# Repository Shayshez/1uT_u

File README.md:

# 1uT_u
1u Version (Pulp Logic) of Temps Utile, 30HP.

For pcb's and panels: https://pushermanproductions.com/product/plum-audio-1u-temps-utile-pcb-and-aluminium-panel-30hp/

Teensy Assembling (with Supervisor):https://youtu.be/IDsQhNgkL-Y

OLED Screen Assembling: https://youtu.be/ywh_6SPNrSg 

** Note for Pusherman v1.0 Pcb's - There is minor silk screen mistake - The Inputs and Outputs not numberd correctly.

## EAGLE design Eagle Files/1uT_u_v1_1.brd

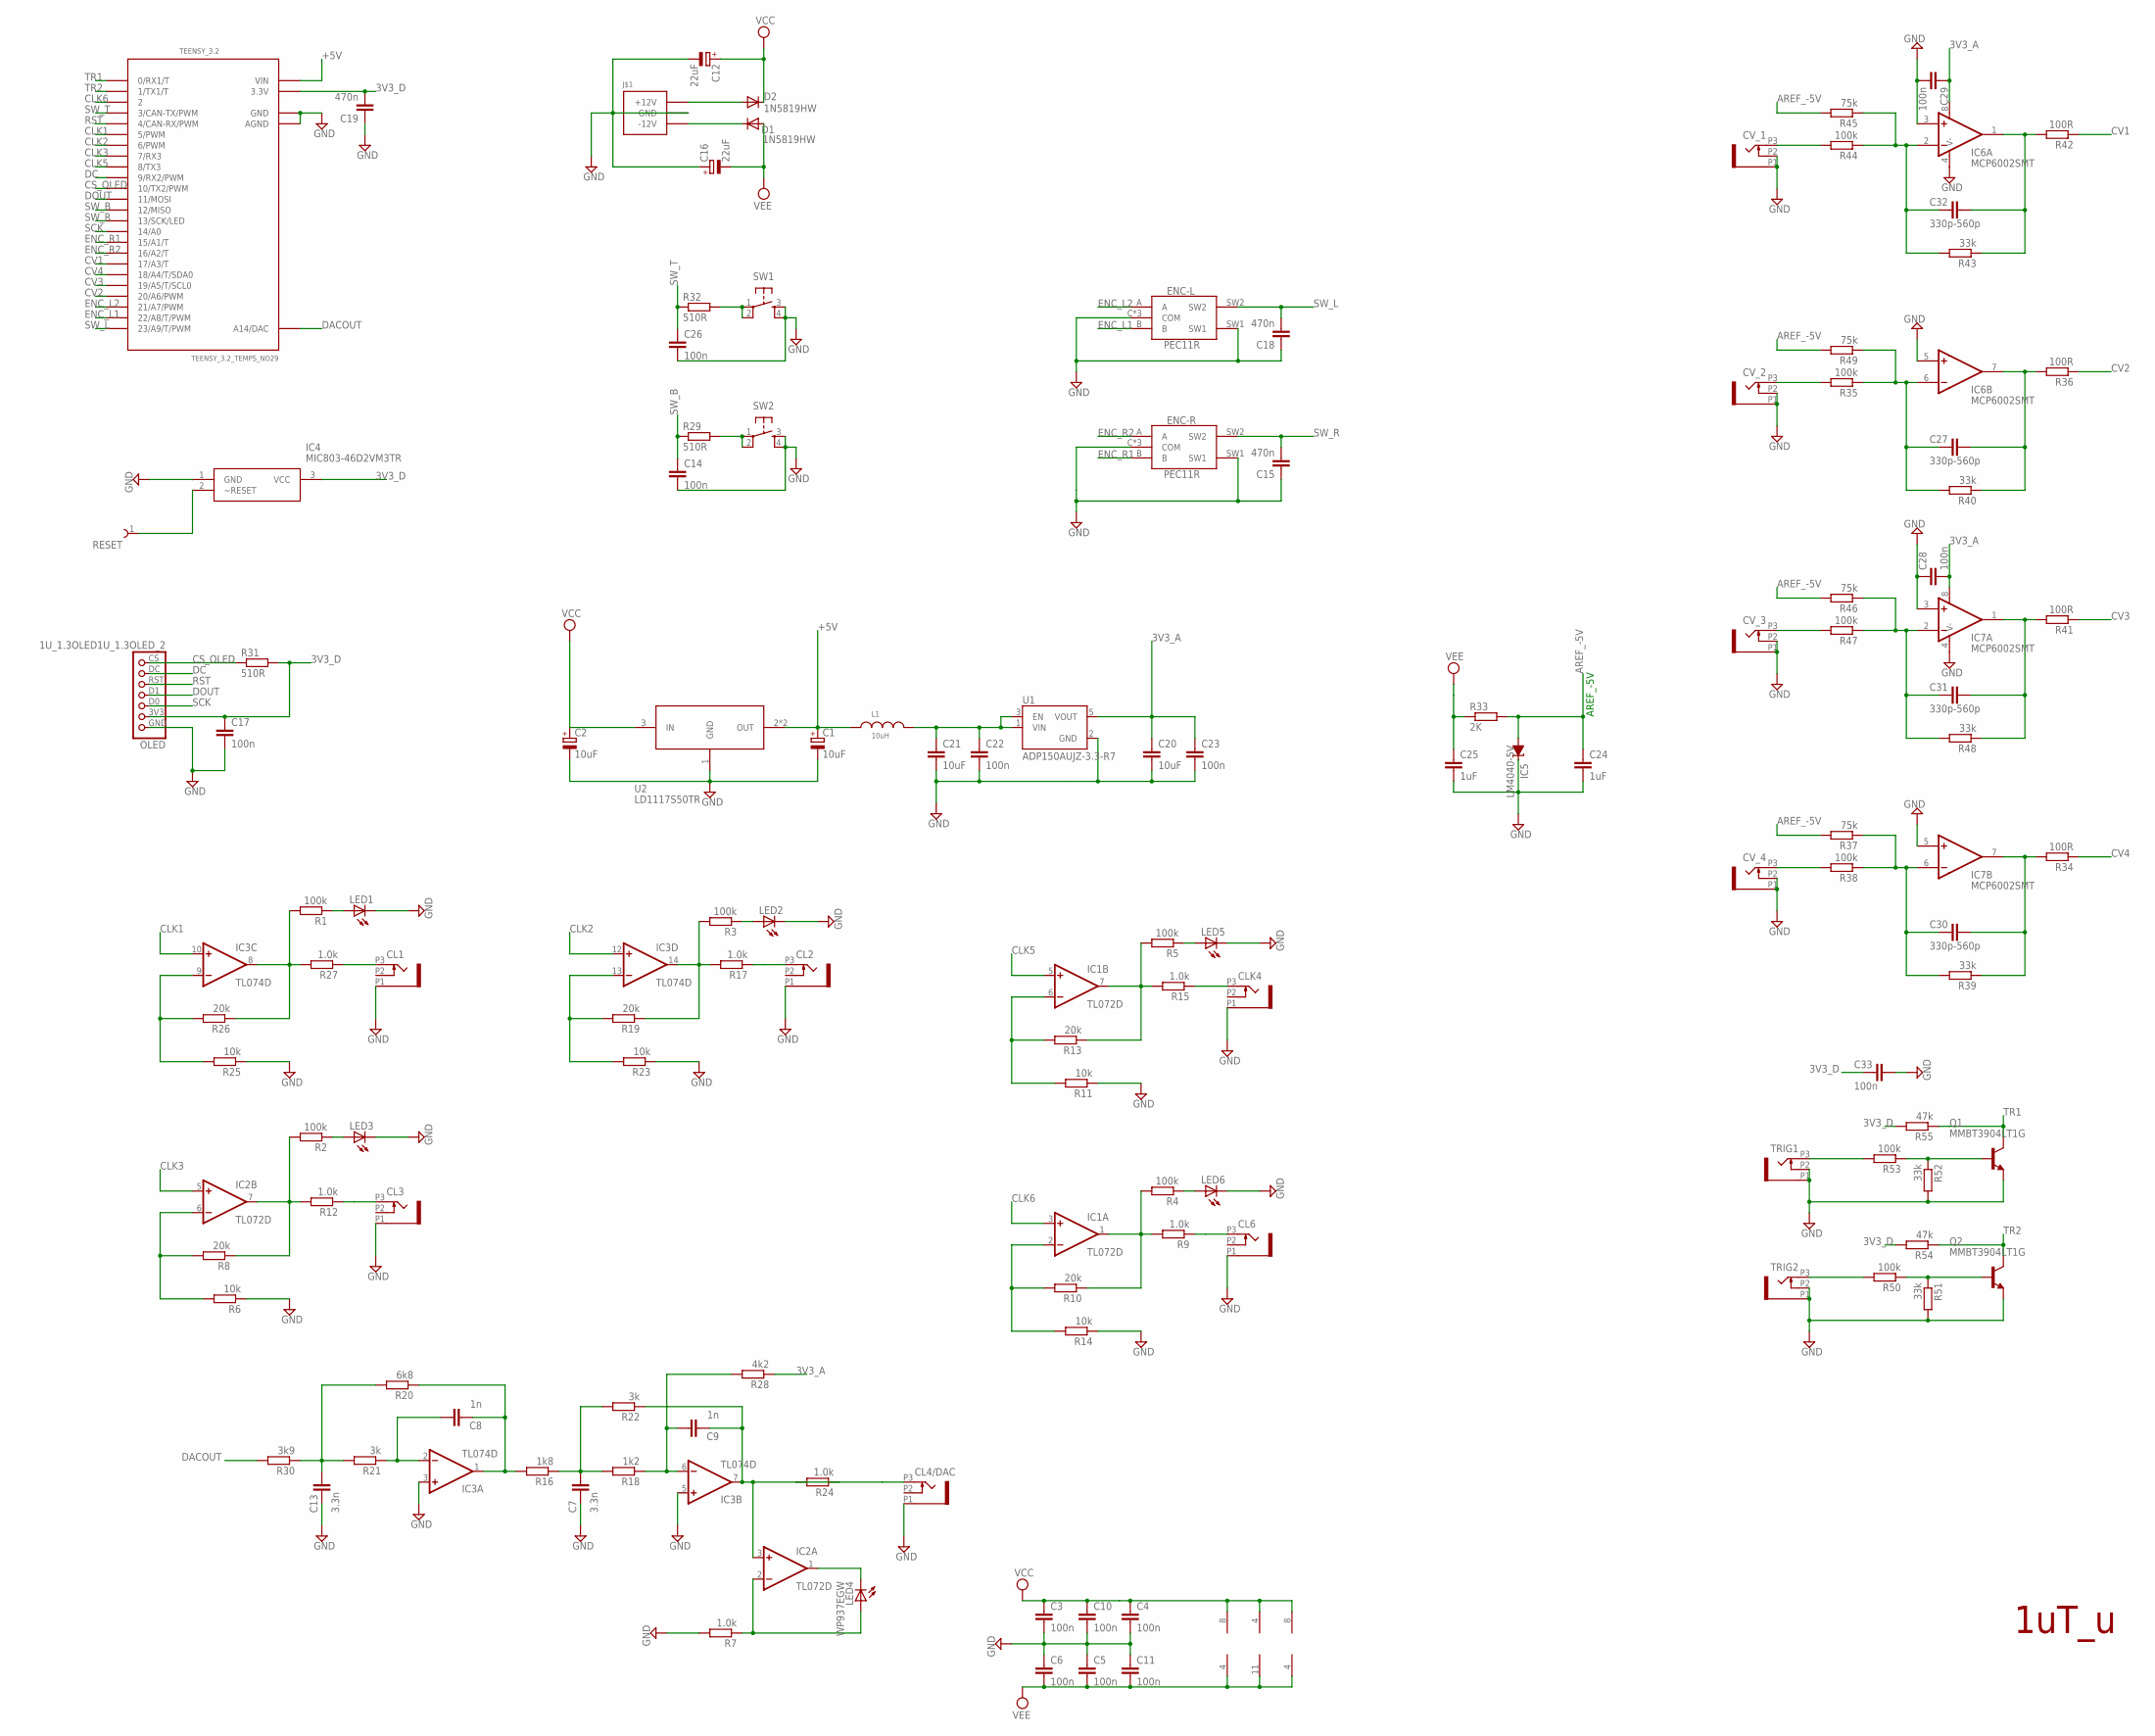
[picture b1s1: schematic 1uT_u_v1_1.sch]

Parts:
C1, C2: 10uF; PANASONIC_B
C3, C4, C5, C6, C10, C11, C14, C17, C22, C23, C26, C28, C29, C33: 100n; C0603
C7, C13: 3.3n; C0603
C8, C9: 1n; C0603
C12, C16: 22uF; PANASONIC_C
C15, C18, C19: 470n; C0603
C20, C21: 10uF; C1206K
C24, C25: 1uF; C0603
C27, C30, C31, C32: 330p-560p; C0603
CL1, CL2, CL3, CL4/DAC, CL6: OG-PJ301_PJ301_THONKICONN; OG-PJ301_WQP_PJ_301M6_NO_HOLE
CLK4: OG-PJ301_PJ301_THONKICONN; OG-PJ301_WQP_PJ_301M6_NO_HOLE
CV_1, CV_2, CV_3, CV_4: OG-PJ301_PJ301_THONKICONN; OG-PJ301_WQP_PJ_301M6_NO_HOLE
D1, D2: 1N5819HW; DIODE_SOD123
ENC-L: PEC11R; PEC11R-4XXXK-SXXXX
ENC-R: PEC11R; PEC11R-4XXXK-SXXXX
IC1, IC2: TL072D; SO08
IC3: TL074D; SO14
IC4: MIC803-46D2VM3TR; SOT95P230X110-3N
IC5: LM4040-5V; DBZ_R-PDSO-G3
IC6, IC7: MCP6002SMT; SOIC8
J$1: POWER_SIMPLE10; POWER_10
L1: 10uH; WE-LQ_M
LED1, LED2, LED3, LED5, LED6: LED3MM
LED4: WP937EGW; LED3MM
OLED: 1U_1.3OLED1U_1.3OLED_2; 1U_1.3OLED_2
Q1, Q2: MMBT3904LT1G; TRANSISTOR_SOT23-BEC
R1, R2, R3, R4, R5, R35, R38, R44, R47, R50, R53: 100k; R0603
R6, R11, R14, R23, R25: 10k; R0603
R7, R9, R12, R15, R17, R24, R27: 1.0k; R0603
R8, R10, R13, R19, R26: 20k; R0603
R16: 1k8; R0603
R18: 1k2; R0603
R20: 6k8; R0603
R21, R22: 3k; R0603
R28: 4k2; R0603
R29, R31, R32: 510R; R0603
R30: 3k9; R0603
R33: 2K; R0603
R34, R36, R41, R42: 100R; R0603
R37, R45, R46, R49: 75k; R0603
R39, R40, R43, R48, R51, R52: 33k; R0603
R54, R55: 47k; R0603
RESET: 61300111121
SW1, SW2: TAC_SWITCHPTH; TACTILE-PTH
TEENSY_3.2: TEENSY_3.2_TEMPS_NO29
TRIG1, TRIG2: OG-PJ301_PJ301_THONKICONN; OG-PJ301_WQP_PJ_301M6_NO_HOLE
U1: ADP150AUJZ-3.3-R7; SOT95P280X100-5N
U2: LD1117S50TR; SOT223

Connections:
3V3_A: C20.1, C23.1, C28.2, C29.1, IC6.8 (V+), IC7.8 (V+), R28.1, U1.5 (VOUT)
3V3_D: C17.1, C19.2, C33.2, IC4.3 (VCC), OLED.3V3, R31.2, R54.2, R55.2, TEENSY_3.2.3.3V
+5V: C1.+, L1.1, TEENSY_3.2.VIN, U2.2 (OUT), U2.4 (OUT)
AREF_-5V: C24.1, IC5.2 (A), R33.2, R37.2, R45.2, R46.2, R49.2
CLK1: IC3.10 (+IN), TEENSY_3.2.5 (5/PWM)
CLK2: IC3.12 (+IN), TEENSY_3.2.6 (6/PWM)
CLK3: IC2.5 (+IN), TEENSY_3.2.7 (7/RX3)
CLK5: IC1.5 (+IN), TEENSY_3.2.8 (8/TX3)
CLK6: IC1.3 (+IN), TEENSY_3.2.2
CS_OLED: OLED.CS, R31.1, TEENSY_3.2.10 (10/TX2/PWM)
CV1: R42.1, TEENSY_3.2.17/A3 (17/A3/T)
CV2: R36.1, TEENSY_3.2.20/A6 (20/A6/PWM)
CV3: R41.1, TEENSY_3.2.19/A5 (19/A5/T/SCL0)
CV4: R34.1, TEENSY_3.2.18/A4 (18/A4/T/SDA0)
DACOUT: R30.2, TEENSY_3.2.RESET/DAC (A14/DAC)
DC: OLED.DC, TEENSY_3.2.9 (9/RX2/PWM)
DOUT: OLED.D1, TEENSY_3.2.11 (11/MOSI)
ENC_L1: ENC-L.B, TEENSY_3.2.22/A8 (22/A8/T/PWM)
ENC_L2: ENC-L.A, TEENSY_3.2.21/A7 (21/A7/PWM)
ENC_R1: ENC-R.B, TEENSY_3.2.15/A1 (15/A1/T)
ENC_R2: ENC-R.A, TEENSY_3.2.16/A2 (16/A2/T)
GND: C1.-, C2.-, C3.2, C4.2, C5.1, C6.1, C7.2, C10.2, C11.1, C12.-, C13.2, C14.2, C15.1, C16.+, C17.2, C18.1, C19.1, C20.2, C21.2, C22.2, C23.2, C24.2, C25.2, C26.2, C28.1, C29.2, C33.1, CL1.P1 (1), CL2.P1 (1), CL3.P1 (1), CL4/DAC.P1 (1), CL6.P1 (1), CLK4.P1 (1), CV_1.P1 (1), CV_1.P2 (2), CV_2.P1 (1), CV_2.P2 (2), CV_3.P1 (1), CV_3.P2 (2), CV_4.P1 (1), CV_4.P2 (2), ENC-L.C (COM), ENC-L.SH1 (COM), ENC-L.SH2 (COM), ENC-L.SW1, ENC-R.C (COM), ENC-R.SH1 (COM), ENC-R.SH2 (COM), ENC-R.SW1, IC3.3 (+IN), IC3.5 (+IN), IC4.1 (GND), IC5.1 (C), IC6.3 (+IN), IC6.4 (V-), IC6.5 (+IN), IC7.3 (+IN), IC7.4 (V-), IC7.5 (+IN), J$1.3 (GND), J$1.4 (GND), J$1.5 (GND), J$1.6 (GND), J$1.7 (GND), J$1.8 (GND), LED1.K (C), LED2.K (C), LED3.K (C), LED5.K (C), LED6.K (C), OLED.GND, Q1.E, Q2.E, R6.1, R7.2, R11.1, R14.1, R23.1, R25.1, R51.2, R52.2, SW1.3, SW1.4, SW2.3, SW2.4, TEENSY_3.2.AGND, TEENSY_3.2.GND, TRIG1.P1 (1), TRIG1.P2 (2), TRIG2.P1 (1), TRIG2.P2 (2), U1.2 (GND), U2.1 (GND)
unnamed: D2.A, J$1.9 (+12V), J$1.10 (+12V)
unnamed: C21.1, C22.1, L1.2, U1.1 (VIN), U1.3 (EN)
unnamed: CV_1.P3 (3), R44.2
unnamed: C32.2, IC6.2 (-IN), R43.2, R44.1, R45.1
unnamed: C32.1, IC6.1 (OUT), R42.2, R43.1
unnamed: R32.2, SW1.1, SW1.2
unnamed: CV_2.P3 (3), R35.2
unnamed: R29.2, SW2.1, SW2.2
unnamed: C27.2, IC6.6 (-IN), R35.1, R40.2, R49.1
unnamed: C27.1, IC6.7 (OUT), R36.2, R40.1
unnamed: CV_3.P3 (3), R47.2
unnamed: C31.2, IC7.2 (-IN), R46.1, R47.1, R48.2
unnamed: C31.1, IC7.1 (OUT), R41.2, R48.1
unnamed: CV_4.P3 (3), R38.2
unnamed: C30.2, IC7.6 (-IN), R37.1, R38.1, R39.2
unnamed: C30.1, IC7.7 (OUT), R34.2, R39.1
unnamed: R53.2, TRIG1.P3 (3)
unnamed: Q1.B, R52.1, R53.1
unnamed: R50.2, TRIG2.P3 (3)
unnamed: Q2.B, R50.1, R51.1
unnamed: CL1.P3 (3), R27.1
unnamed: CL3.P3 (3), R12.1
unnamed: IC1.6 (-IN), R11.2, R13.2
unnamed: IC1.7 (OUT), R5.2, R13.1, R15.2
unnamed: IC3.13 (-IN), R19.2, R23.2
unnamed: IC3.9 (-IN), R25.2, R26.2
unnamed: IC3.8 (OUT), R1.2, R26.1, R27.2
unnamed: CLK4.P3 (3), R15.1
unnamed: IC3.14 (OUT), R3.2, R17.2, R19.1
unnamed: CL2.P3 (3), R17.1
unnamed: IC2.6 (-IN), R6.2, R8.2
unnamed: IC2.7 (OUT), R2.2, R8.1, R12.2
unnamed: IC1.2 (-IN), R10.2, R14.2
unnamed: IC2.1 (OUT), LED4.K (C)
unnamed: IC2.2 (-IN), LED4.A, R7.1
unnamed: CL4/DAC.P3 (3), R24.1
unnamed: IC1.1 (OUT), R4.2, R9.2, R10.1
unnamed: CL6.P3 (3), R9.1
unnamed: C9.2, IC2.3 (+IN), IC3.7 (OUT), R22.1, R24.2
unnamed: D1.C, J$1.1 (-12V), J$1.2 (-12V)
unnamed: C13.1, R20.2, R21.2, R30.1
unnamed: C8.1, IC3.2 (-IN), R21.1
unnamed: C8.2, IC3.1 (OUT), R16.2, R20.1
unnamed: C7.1, R16.1, R18.2, R22.2
unnamed: C9.1, IC3.6 (-IN), R18.1, R28.2
unnamed: LED3.A, R2.1
unnamed: LED1.A, R1.1
unnamed: LED2.A, R3.1
unnamed: LED5.A, R5.1
unnamed: LED6.A, R4.1
unnamed: IC4.2 (~RESET), RESET.1
RST: OLED.RST, TEENSY_3.2.4 (4/CAN-RX/PWM)
SCK: OLED.D0, TEENSY_3.2.14/A0
SW_B: C14.1, R29.1, TEENSY_3.2.12 (12/MISO)
SW_L: C18.2, ENC-L.SW2, TEENSY_3.2.23/A9 (23/A9/T/PWM)
SW_R: C15.2, ENC-R.SW2, TEENSY_3.2.13 (13/SCK/LED)
SW_T: C26.1, R32.1, TEENSY_3.2.3 (3/CAN-TX/PWM)
TR1: Q1.C, R55.1, TEENSY_3.2.0 (0/RX1/T)
TR2: Q2.C, R54.1, TEENSY_3.2.1 (1/TX1/T)
VCC: C2.+, C3.1, C4.1, C10.1, C12.+, D2.C, IC1.8 (V+), IC2.8 (V+), IC3.4 (V+), U2.3 (IN)
VEE: C5.2, C6.2, C11.2, C16.-, C25.1, D1.A, IC1.4 (V-), IC2.4 (V-), IC3.11 (V-), R33.1

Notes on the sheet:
AREF_-5V
1uT_u

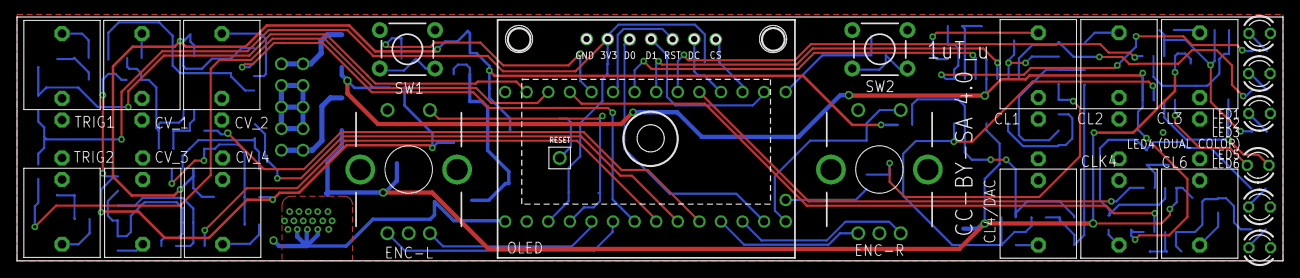
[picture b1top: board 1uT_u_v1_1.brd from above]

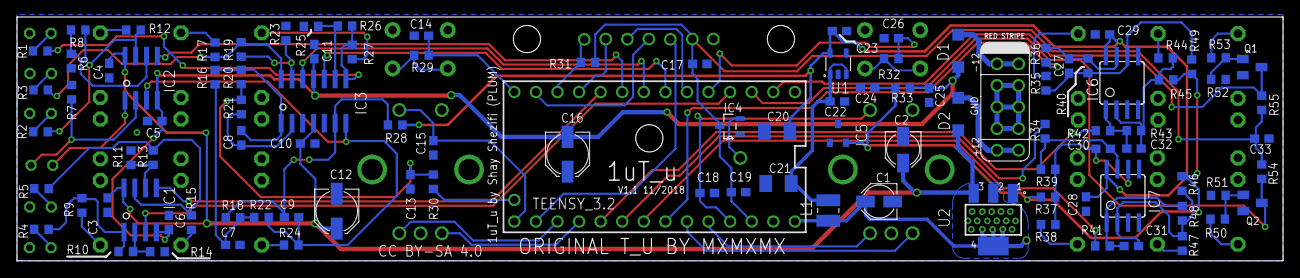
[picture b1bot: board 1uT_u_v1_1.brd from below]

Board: 2 copper layers, 149.0 x 28.7 mm, 128 parts (104 on the bottom side), 83 nets.

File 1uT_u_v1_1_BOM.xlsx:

Qty | Value | Device | Package |  | Parts | Description | ALLIED_NUMBER | ALLIED_PRICE-STOCK | ARROW_PART_NUMBER | ARROW_PRICE-STOCK | AVAILABILITY | DESCRIPTION | HEIGHT | MANUFACTURER_NAME | MANUFACTURER_PART_NUMBER | MF | MP | MPN | OC_FARNELL | OC_NEWARK | PACKAGE | PRICE | RS_PART_NUMBER | RS_PRICE-STOCK | SPICEPREFIX | WE-NUMBER
4 | 100R | R-EU_R0603 | R0603 | 603-RC0603FR-07100RL | R34, R36, R41, R42 | RESISTOR, European symbol |  |  |  |  |  |  |  |  |  |  |  |  |  |  |  |  |  |  | R
3 | 510R | R-EU_R0603 | R0603 | 603-RC0603FR-07510RL | R29, R31, R32 | RESISTOR, European symbol |  |  |  |  |  |  |  |  |  |  |  |  |  |  |  |  |  |  | R
7 | 1.0k | R-EU_R0603 | R0603 | 603-RC0603FR-071KL | R7, R9, R12, R15, R17, R24, R27 | RESISTOR, European symbol |  |  |  |  |  |  |  |  |  |  |  |  |  |  |  |  |  |  | R
1 | 1k2 | R-EU_R0603 | R0603 | 603-RC0603FR-101K2L | R18 | RESISTOR, European symbol |  |  |  |  |  |  |  |  |  |  |  |  |  |  |  |  |  |  | R
1 | 1k8 | R-EU_R0603 | R0603 | 603-RC0603FR-071K8L | R16 | RESISTOR, European symbol |  |  |  |  |  |  |  |  |  |  |  |  |  |  |  |  |  |  | R
1 | 2K | R-EU_R0603 | R0603 | 603-RC0603FR-102KL | R33 | RESISTOR, European symbol |  |  |  |  |  |  |  |  |  |  |  |  |  |  |  |  |  |  | R
2 | 3k | R-EU_R0603 | R0603 | 603-RC0603FR-073KL | R21, R22 | RESISTOR, European symbol |  |  |  |  |  |  |  |  |  |  |  |  |  |  |  |  |  |  | R
1 | 3k9 | R-EU_R0603 | R0603 | 603-RC0603FR-133K9L | R30 | RESISTOR, European symbol |  |  |  |  |  |  |  |  |  |  |  |  |  |  |  |  |  |  | R
1 | 4k2 | R-EU_R0603 | R0603 | 603-RC0603FR-074K22L | R28 | RESISTOR, European symbol |  |  |  |  |  |  |  |  |  |  |  |  |  |  |  |  |  |  | R
1 | 6k8 | R-EU_R0603 | R0603 | 603-RC0603FR-106K8L | R20 | RESISTOR, European symbol |  |  |  |  |  |  |  |  |  |  |  |  |  |  |  |  |  |  | R
5 | 10k | R-EU_R0603 | R0603 | 603-RC0603FR-0710KL | R6, R11, R14, R23, R25 | RESISTOR, European symbol |  |  |  |  |  |  |  |  |  |  |  |  |  |  |  |  |  |  | R
5 | 20k | R-EU_R0603 | R0603 | 603-RC0603FR-1020KL | R8, R10, R13, R19, R26 | RESISTOR, European symbol |  |  |  |  |  |  |  |  |  |  |  |  |  |  |  |  |  |  | R
6 | 33k | R-EU_R0603 | R0603 | 603-RC0603FR-0733KL | R39, R40, R43, R48, R51, R52 | RESISTOR, European symbol |  |  |  |  |  |  |  |  |  |  |  |  |  |  |  |  |  |  | R
2 | 47k | R-EU_R0603 | R0603 | 603-RC0603FR-0747KL | R54, R55 | RESISTOR, European symbol |  |  |  |  |  |  |  |  |  |  |  |  |  |  |  |  |  |  | R
4 | 75k | R-EU_R0603 | R0603 | 603-AC0603FR-0775KL | R37, R45, R46, R49 | RESISTOR, European symbol |  |  |  |  |  |  |  |  |  |  |  |  |  |  |  |  |  |  | R
11 | 100k | R-EU_R0603 | R0603 | 603-RC0603FR-07100KL | R1, R2, R3, R4, R5, R35, R38, R44, R47, R50, R53 | RESISTOR, European symbol |  |  |  |  |  |  |  |  |  |  |  |  |  |  |  |  |  |  | R
4 | 330p-560p | C-EUC0603 | C0603 |  | C27, C30, C31, C32 | CAPACITOR, European symbol
2 | 1n | C-EUC0603 | C0603 |  | C8, C9 | CAPACITOR, European symbol
2 | 3.3n | C-EUC0603 | C0603 |  | C7, C13 | CAPACITOR, European symbol
14 | 100n | C-EUC0603 | C0603 |  | C3, C4, C5, C6, C10, C11, C14, C17, C22, C23, C26, C28, C29, C33 | CAPACITOR, European symbol
3 | 470n | C-EUC0603 | C0603 |  | C15, C18, C19 | CAPACITOR, European symbol
2 | 1uF | C-EUC0603 | C0603 |  | C24, C25 | CAPACITOR, European symbol
2 | 10uF | C-EUC1206K | C1206K |  | C20, C21 | CAPACITOR, European symbol
2 | 10uF | CPOL-EUB | PANASONIC_B |  | C1, C2 | POLARIZED CAPACITOR, European symbol |  |  |  |  |  |  |  |  |  |  |  |  |  |  |  |  |  |  | C
2 | 22uF | CPOL-EUC | PANASONIC_C |  | C12, C16 | POLARIZED CAPACITOR, European symbol |  |  |  |  |  |  |  |  |  |  |  |  |  |  |  |  |  |  | C
2 | 1N5819HW | DIODE_DIODE-SOD123 | DIODE_SOD123 |  | D1, D2 | DIODE
1 | 10uH | WE-LQ_1210_744032001 | WE-LQ_M | 963-LB3218T100K | L1 | SMD Inductor |  |  |  |  |  |  |  |  |  |  |  |  |  |  |  |  |  |  |  | 744032001/1uH
1 | LM4040-5V | LM4041B12DBZ | DBZ_R-PDSO-G3 |  | IC5 | PRECISION MICROPOWER SHUNT VOLTAGE REFERENCE |  |  |  |  |  |  |  |  |  |  |  | LM4041B12IDBZR | 1575212 | 58K5882
2 | TL072D | TL072D | SO08 |  | IC1, IC2 | OP AMP
1 | TL074D | TL074D | SO14 |  | IC3 | OP AMP
2 | MCP6002SMT | MCP6002SMT | SOIC8 |  | IC6, IC7 | Dual General Op Amp
1 | LD1117S50TR | LD1117S50TR | SOT223 |  | U2 | http://octopart.com/ld1117s50tr-stmicroelectronics-529395 |  |  |  |  | Good | LD1117 Series 1300 mA 5 V Fixed Output Positive Voltage LDO Regulator - SOT-223 |  |  |  | STMicroelectronics | LD1117S50TR |  |  |  | SOT-223 STMicroelectronics | 0.19 USD
2 | MMBT3904LT1G | TRANSISTOR_MMBT3904LT1-NPN-SOT23-BEC | TRANSISTOR_SOT23-BEC |  | Q1, Q2 | NPN Transistror
1 | MIC803-46D2VM3TR | MIC803-46D2VM3TR | SOT95P230X110-3N |  | IC4 | 3-pin Microprocessor Supervosor Circui |  |  | MIC803-46D2VM3TR |  |  | 3-pin Microprocessor Supervosor Circui | mm | Micrel | MIC803-46D2VM3TR
1 | ADP150AUJZ-3.3-R7 | ADP150AUJZ-3.3-R7 | SOT95P280X100-5N |  | U1 | IC REG LINEAR 2V 150MA 5TSOT |  |  |  |  | Good | LDO Regulator Pos 2V 0.15A 5-Pin TSOT T/R |  |  |  | Analog Devices | ADP150AUJZ-2.0-R7 |  |  |  | TSOT-23 Analog Devices | 0.65 USD
2 | Tact Switch | TACT_SWITCHPTH | TACTILE-PTH |  | SW1, SW2 | Momentary Switch
2 | PEC11R | PEC11R | PEC11R-4XXXK-SXXXX |  | ENC-L, ENC-R | Incremental encoder 24 detents 24 pulses Bourns 24 Pulse Incremental Mechanical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 | 70407906 | https://www.alliedelec.com/bourns-pec11r-4215k-s0024/70407906/ | PEC11R-4215K-S0024 | http://uk.rs-online.com/web/p/products/1674651 |  | Incremental encoder 24 detents 24 pulses Bourns 24 Pulse Incremental Mechanical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 | mm | Bourns | PEC11R-4215K-S0024 |  |  |  |  |  |  |  | 1674651 | http://uk.rs-online.com/web/p/products/1674651
1 | TEENSY_3.2 | TEENSY_3.2 | TEENSY_3.2 |  | TEENSY_3.2 | https://store.oshpark.com/products/teensy-3-1
1 | OLED | 1U_1.3_OLED_2 | 1U_1.3_OLED_2 |  | OLED | https://github.com/Shayshez/1_3_OLED_FOR_1U
1 | 2X5 Pin Header | POWER | POWER_10 |  | J1
5 | LED | LED3MM | LED3MM |  | LED1, LED2, LED3, LED5, LED6 | LED
1 | LED BI COLOUR (RED/GREEN) | LED3MM | LED3MM | WP937EGW | LED4 | LED BI BOLOUR
12 | PJ301_THONKICONN | THONKICONN | WQP_PJ_301M6 |  | CL1, CL2, CL3, CL4, CL4/DAC, CL5, CV_1, CV_2, CV_3, CV_4, TRIG1, TRIG2

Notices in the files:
Eagle Files/1uT_u_v1_1.brd:
CC BY-SA 4.0
parts and their libraries:
Wurth_Elektronik_Passive_rev17b: Copyright: Würth Elektronik
